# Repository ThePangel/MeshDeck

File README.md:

# MeshDeck

Standalone ESP32-S3 powered Meshtastic device!

---

Meshdeck is a Standalone Meshtastic device powered by an ESP32-S3, It has a built in keyboard and a touchscreen allowing you to communicate off grid without any phone, completely standalone.

I made this because I wanted to get into Meshtastic, and RF radio stuff, and the best way of learning is making

The keyboard is just a button matrix connected to an RP2040 which will act as an i2c slave and send keycodes to the esp. 

---

---

## Bill of Materials (BOM)

| Designator | Footprint                                | Quantity | Value           | LCSC Part #     |
|------------|------------------------------------------|----------|-----------------|-----------------|
| C1         | C0402                                    | 1        | 22uF            | C105226         |
| C10, C11, C12, C19 | C0402                            | 4        | 10uF            | C15525          |
| C13, C2, C20, C22, C23, C24, C25, C26, C27, C28, C30, C31, C32, C35, C36, C37, C38, C39, C4, C40, C41, C42, C43, C44, C45, C46, C47, C48, C49, C5, C50, C51, C52, C53, C54, C55, C56, C57, C58, C59, C60, C61, C62, C63, C64, C65, C66, C67, C68, C69, C70 | C0402 | 51 | 0.1uF | C1525 |
| C14, C15   | C0402                                    | 2        | 12pF            | C1547           |
| C16, C18, C21, C29, C3, C7 | C0402                   | 6        | 1uF             | C14445          |
| C17        | C0402                                    | 1        | 1Nf             | C1523           |
| C33, C34   | C0402                                    | 2        | 15pF            | C1548           |
| C6, C8, C9 | C0402                                    | 3        | 4.7 uF          | C23733          |
| CARD1      | TF-SMD_503398-1892                       | 1        | 503398-1892     | C428492         |
| CN1        | COMM-SMD_18P-L10.1-W9.7-P1.1-TL_L76-LB  | 1        | ATGM336H-6N-74  | C5804601        |
| D1         | SOT-666-6_L1.6-W1.2-P0.50-LS1.6-BR      | 1        | USBLC6-2P6      | C15999          |
| D10-D37    | SOD-123_L2.8-W1.8-LS3.7-RD              | 36       | 1N4148W T4      | C2099           |
| H1         | CONN-SMD_2P-P2.00_XUNPU_WAFER-PH2.0-2PWB| 1        | WAFER-PH2.0-2PWB| C3029440        |
| J1         | PinHeader_1x03_P2.54mm_Horizontal       | 1        | Conn_01x03_MountingPin | - |
| J2         | PinSocket_2x05_P2.54mm_Horizontal       | 1        | Conn_02x05_Odd_Even | - |
| L1         | L0402                                    | 1        | 0.47 µH         | C5788770        |
| L2         | L0402-RD                                 | 1        | 47nH            | C471397         |
| LED1, LED3 | LED0805-R-RD                             | 2        | 0805G (Green)   | C2297           |
| LED2       | LED0603-RD                               | 1        | Blue light 0603 | C2288           |
| LED4       | LED0402-RD                               | 1        | red             | C130719         |
| R1, R13, R17-R25 | R0402                              | 9        | 10KOhm          | C25531          |
| R10, R9    | R0402                                    | 2        | 1.8k            | C25871          |
| R11, R16   | R0402                                    | 2        | 10K             | C25744          |
| R12, R14, R15, R2-R4 | R0402                          | 6        | 0 Ohm           | C17168          |
| R19, R20   | R0402                                    | 2        | 220ohm          | C25091          |
| R26-R64    | R0402                                    | 37       | 1k              | C11702          |
| R5, R6     | R0402                                    | 2        | 5.1k            | C25905          |
| R62, R63   | R0603                                    | 2        | 100k            | C14675          |
| R7         | R0402                                    | 1        | 1.5K            | C25867          |
| R8         | R0402                                    | 1        | 1.5K            | C25867          |
| RF1, RF2   | SMA-SMD_HJ-SMA023                        | 2        | HJ-SMA023       | C1509219        |
| SW1-SW39   | SW-SMD_4P-L5.2-W5.2-P3.70-LS6.5         | 38       | 4*4*1.7         | C10852          |
| SW3        | KEY-TH_4P-L7.5-W6.8-P4.50-LS7.2         | 1        | SKHHLVA010      | C110289         |
| U1         | WIRELM-SMD_ESP32-S3-WROOM-1U            | 1        | ESP32-S3-WROOM-1U-N16R8 | C3013946 |
| U10        | CRYSTAL-SMD_4P-L3.2-W2.5-BL             | 1        | ABM8-272-T3_C20625731 | C20625731 |
| U2         | WIRELM-SMD_SX1278S165SY-T-X1            | 1        | SX1262S8S+T-X1  | C718838         |
| U3         | VSON-6_L1.5-W1.5-P0.50-TL               | 1        | TPS6282533DMQR  | C3189971        |
| U4         | QFN-16_L3.0-W3.0-P0.50-TL-EP1.7         | 1        | BQ24074RGTR     | C54313          |
| U5         | OSC-TH_BD2.0-P0.50                      | 1        | RN32768114      | C7206316        |
| U6         | 2.8 SPI LCD TFT ST7789                  | 1        | ~               | -               |
| U7         | SOIC-14_L8.7-W3.9-P1.27-LS6.0-BL        | 1        | CD4013BM        | C347580         |
| U8         | LQFN-56_L7.0-W7.0-P0.4-EP               | 1        | RP2040          | C2040           |
| U9         | SOIC-8_L5.3-W5.3-P1.27-LS8.0-BL         | 1        | W25Q128JVSIQTR  | C97521          |
| USBC1      | USB-C_SMD-TYPE-C-31-M-12_1              | 1        | TYPE-C-31-M-12  | C165948         |

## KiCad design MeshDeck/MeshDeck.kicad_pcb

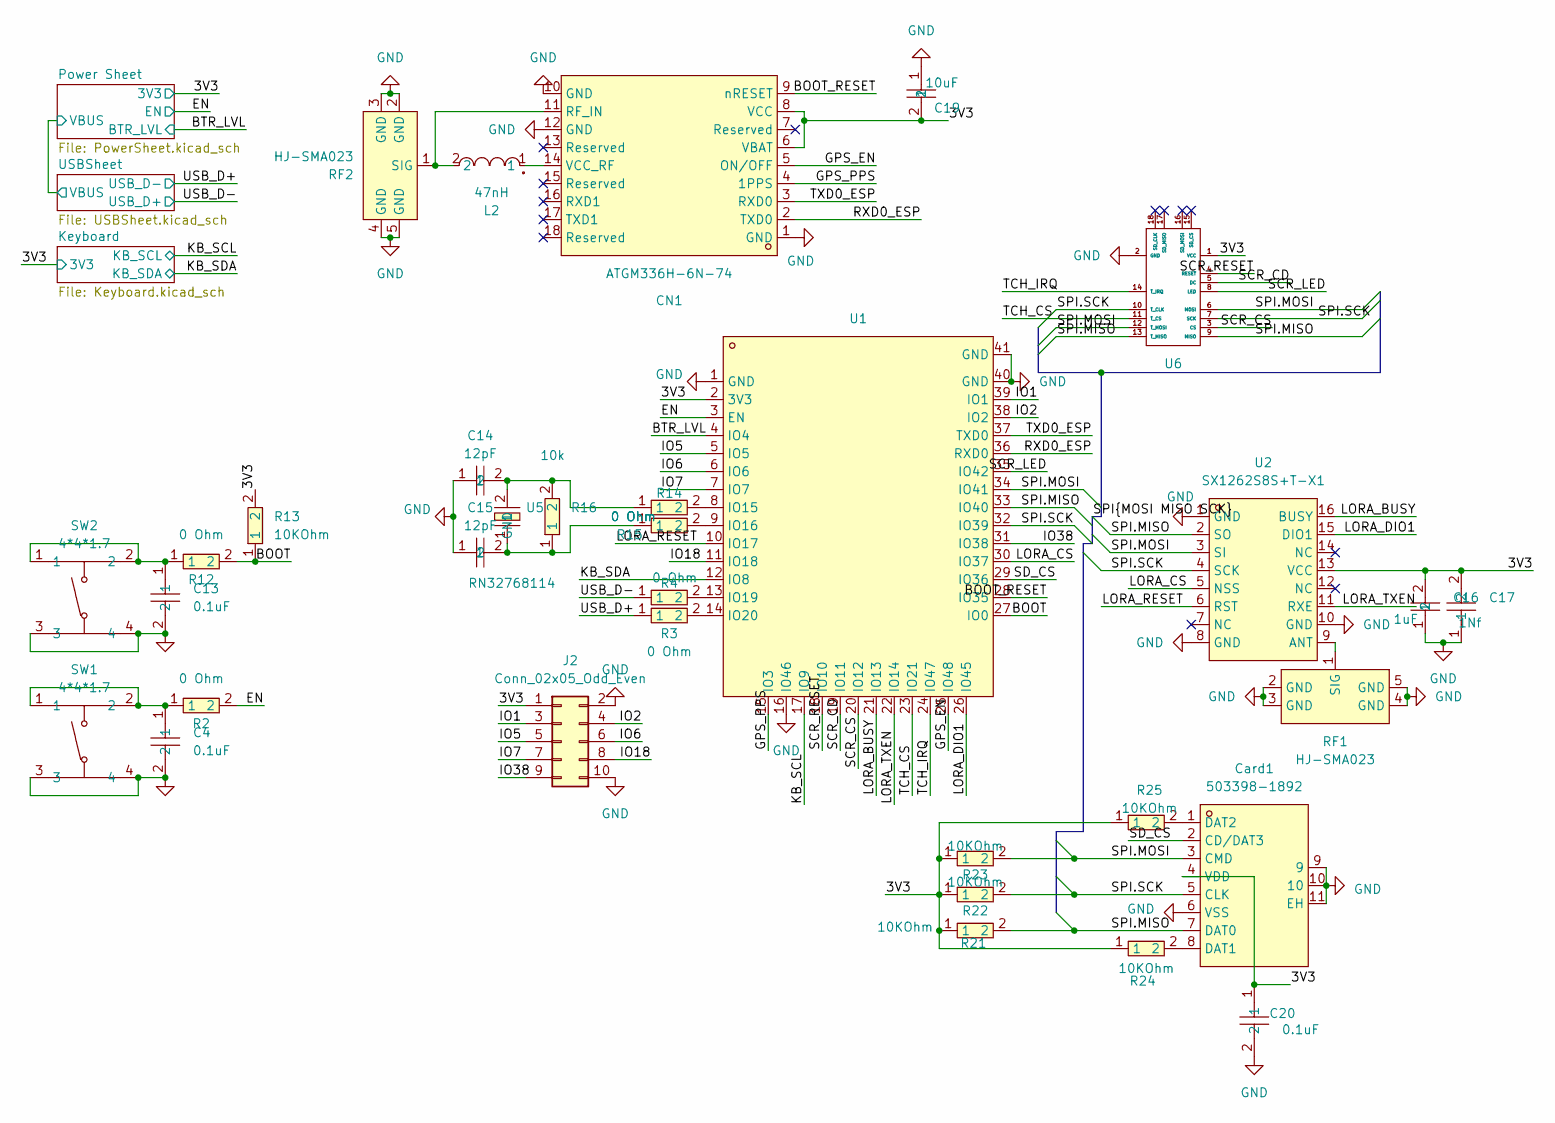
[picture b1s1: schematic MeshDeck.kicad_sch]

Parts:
C4, C13, C20: 0.1uF; C0402; LCSC Part C1525
C14, C15: 12pF; C0402; LCSC Part C1547
C16: 1uF; C0402; LCSC Part C14445
C17: 1Nf; C0402; LCSC Part C1523
C19: 10uF; C0402; LCSC Part C15525
CN1: ATGM336H-6N-74; COMM-SMD_18P-L10.1-W9.7-P1.1-TL_L76-LB; LCSC Part C5804601
Card1: 503398-1892; TF-SMD_503398-1892; LCSC Part C428492
J2: Conn_02x05_Odd_Even; PinSocket_2x05_P2.54mm_Horizontal
L2: 47nH; L0402-RD; LCSC Part C471397
R2, R3, R4, R12, R14, R15: 0 Ohm; R0402; LCSC Part C17168
R13, R21, R22, R23, R24, R25: 10KOhm; R0402; LCSC Part C25531
R16: 10k; R0402; LCSC Part C25744
RF1, RF2: HJ-SMA023; SMA-SMD_HJ-SMA023; LCSC Part C1509219
SW1, SW2: 4*4*1.7; SW-SMD_4P-L5.2-W5.2-P3.70-LS6.5; LCSC Part C10852
U1: ESP32-S3-WROOM-1U-N16R8; WIRELM-SMD_ESP32-S3-WROOM-1U; LCSC Part C3013946
U2: SX1262S8S+T-X1; WIRELM-SMD_SX1278S165SY-T-X1; LCSC Part C718838
U5: RN32768114; OSC-TH_BD2.0-P0.50; LCSC Part C7206316
U6: 2.8 SPI LCD TFT ST7789

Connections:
/3V3: C16.2, C17.2, C19.2, C20.1, CN1.6 (VBAT), CN1.8 (VCC), Card1.4 (VDD), J2.1, R13.2, R21.1, R22.1, R23.1, R24.1, R25.1, U1.2 (3V3), U2.13 (VCC), U6.1 (VCC); also elsewhere on the board
/BOOT: R12.2, R13.1, U1.27 (IO0)
/BOOT_RESET: CN1.9 (nRESET), U1.28 (IO35)
/BTR_LVL: U1.4 (IO4); also elsewhere on the board
/EN: R2.2, U1.3 (EN); also elsewhere on the board
/GPS_EN: CN1.5 (ON/OFF), U1.25 (IO48)
/GPS_PPS: CN1.4 (1PPS), U1.15 (IO3)
/IO1: J2.3, U1.39 (IO1)
/IO2: J2.4, U1.38 (IO2)
/IO5: J2.5, U1.5 (IO5)
/IO6: J2.6, U1.6 (IO6)
/IO7: J2.7, U1.7 (IO7)
/IO18: J2.8, U1.11 (IO18)
/IO38: J2.9, U1.31 (IO38)
/KB_SCL: U1.17 (IO9); also elsewhere on the board
/KB_SDA: U1.12 (IO8); also elsewhere on the board
/LORA_BUSY: U1.21 (IO13), U2.16 (BUSY)
/LORA_CS: U1.30 (IO37), U2.5 (NSS)
/LORA_DIO1: U1.26 (IO45), U2.15 (DIO1)
/LORA_RESET: U1.10 (IO17), U2.6 (RST)
/LORA_TXEN: U1.22 (IO14), U2.11 (RXE)
/RXD0_ESP: CN1.2 (TXD0), U1.36 (RXD0)
/SCR_CD: U1.19 (IO11), U6.5 (DC)
/SCR_CS: U1.20 (IO12), U6.3 (CS)
/SCR_LED: U1.35 (IO42), U6.8 (LED)
/SCR_RESET: U1.18 (IO10), U6.4 (RESET)
/SD_CS: Card1.2 (CD/DAT3), U1.29 (IO36)
/SPI.MISO: Card1.7 (DAT0), R21.2, U1.33 (IO40), U2.2 (SO), U6.9 (MISO), U6.13 (T_MISO)
/SPI.MOSI: Card1.3 (CMD), R23.2, U1.34 (IO41), U2.3 (SI), U6.6 (MOSI), U6.12 (T_MOSI)
/SPI.SCK: Card1.5 (CLK), R22.2, U1.32 (IO39), U2.4 (SCK), U6.7 (SCK), U6.10 (T_CLK)
/TCH_CS: U1.23 (IO21), U6.11 (T_CS)
/TCH_IRQ: U1.24 (IO47), U6.14 (T_IRQ)
/TXD0_ESP: CN1.3 (RXD0), U1.37 (TXD0)
/USB_D+: R3.1; also elsewhere on the board
/USB_D-: R4.1; also elsewhere on the board
GND: C4.2, C13.2, C14.1, C15.1, C16.1, C17.1, C19.1, C20.2, CN1.1 (GND), CN1.10 (GND), CN1.12 (GND), Card1.6 (VSS), Card1.9, Card1.10, Card1.11 (EH), J2.2, J2.10, RF1.2 (GND), RF1.3 (GND), RF1.4 (GND), RF1.5 (GND), RF2.2 (GND), RF2.3 (GND), RF2.4 (GND), RF2.5 (GND), SW1.3, SW1.4, SW2.3, SW2.4, U1.1 (GND), U1.16 (IO46), U1.40 (GND), U1.41 (GND), U2.1 (GND), U2.8 (GND), U2.10 (GND), U6.2 (GND); also elsewhere on the board
unnamed: C4.1, R2.1, SW1.1, SW1.2
unnamed: C13.1, R12.1, SW2.1, SW2.2
unnamed: C15.2, R15.1, R16.1, U5.1
unnamed: CN1.11 (RF_IN), L2.2, RF2.1 (SIG)
unnamed: CN1.14 (VCC_RF), L2.1
unnamed: Card1.8 (DAT1), R24.2
unnamed: Card1.1 (DAT2), R25.2
unnamed: RF1.1 (SIG), U2.9 (ANT)
unnamed: R14.2, U1.8 (IO15)
unnamed: R15.2, U1.9 (IO16)
unnamed: R4.2, U1.13 (IO19)
unnamed: R3.2, U1.14 (IO20)
unnamed: C14.2, R14.1, R16.2, U5.2 (GND)

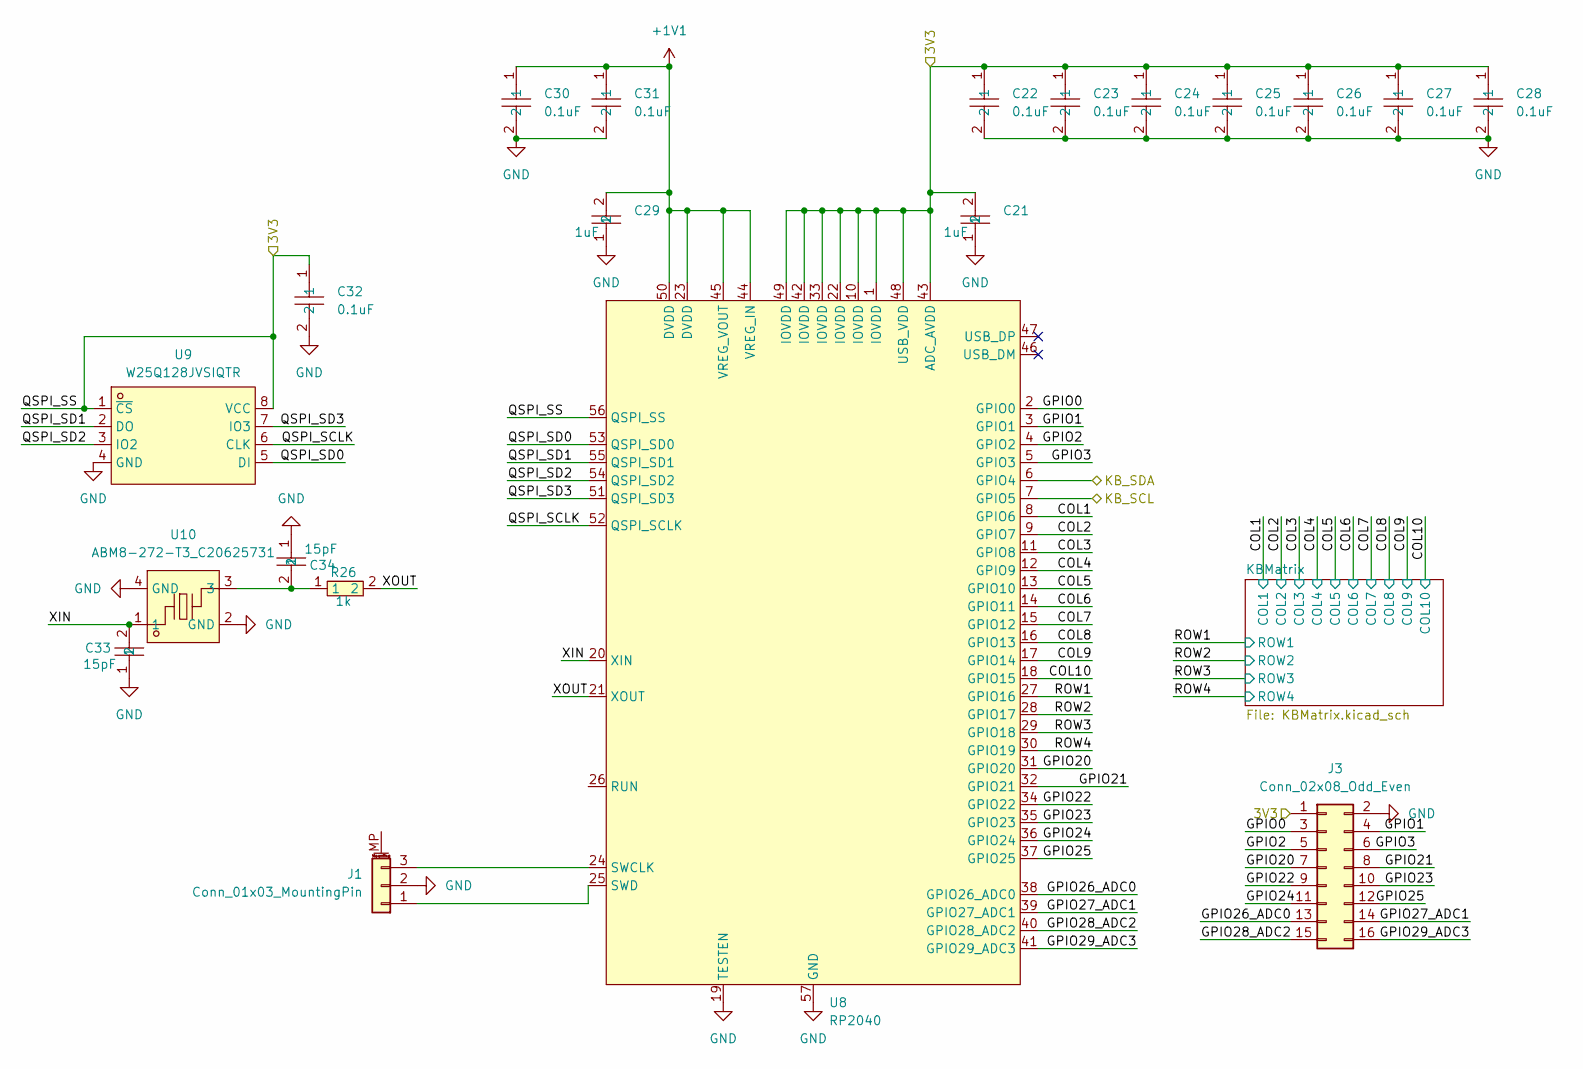
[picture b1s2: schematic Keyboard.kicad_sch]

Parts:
C21, C29: 1uF; C0402; LCSC Part C14445
C22, C23, C24, C25, C26, C27, C28, C30, C31, C32: 0.1uF; C0402; LCSC Part C1525
C33, C34: 15pF; C0402; LCSC Part C1548
J1: Conn_01x03_MountingPin; PinHeader_1x03_P2.54mm_Horizontal
J3: Conn_02x08_Odd_Even; PinSocket_2x08_P2.54mm_Horizontal
R26: 1k; R0402; LCSC Part C11702
U8: RP2040; LQFN-56_L7.0-W7.0-P0.4-EP; LCSC Part C2040
U9: W25Q128JVSIQTR; SOIC-8_L5.3-W5.3-P1.27-LS8.0-BL; LCSC Part C97521
U10: ABM8-272-T3_C20625731; CRYSTAL-SMD_4P-L3.2-W2.5-BL; LCSC Part C20625731

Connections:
+1V1: C29.2, C30.1, C31.1, U8.23 (DVDD), U8.44 (VREG_IN), U8.45 (VREG_VOUT), U8.50 (DVDD)
/3V3: C21.2, C22.1, C23.1, C24.1, C25.1, C26.1, C27.1, C28.1, C32.1, J3.1, U8.1 (IOVDD), U8.10 (IOVDD), U8.22 (IOVDD), U8.33 (IOVDD), U8.42 (IOVDD), U8.43 (ADC_AVDD), U8.48 (USB_VDD), U8.49 (IOVDD), U8.56 (QSPI_SS), U9.1 (~CS), U9.8 (VCC); also elsewhere on the board
/KB_SCL: U8.7 (GPIO5); also elsewhere on the board
/KB_SDA: U8.6 (GPIO4); also elsewhere on the board
/Keyboard/COL1: U8.8 (GPIO6); also elsewhere on the board
/Keyboard/COL2: U8.9 (GPIO7); also elsewhere on the board
/Keyboard/COL3: U8.11 (GPIO8); also elsewhere on the board
/Keyboard/COL4: U8.12 (GPIO9); also elsewhere on the board
/Keyboard/COL5: U8.13 (GPIO10); also elsewhere on the board
/Keyboard/COL6: U8.14 (GPIO11); also elsewhere on the board
/Keyboard/COL7: U8.15 (GPIO12); also elsewhere on the board
/Keyboard/COL8: U8.16 (GPIO13); also elsewhere on the board
/Keyboard/COL9: U8.17 (GPIO14); also elsewhere on the board
/Keyboard/COL10: U8.18 (GPIO15); also elsewhere on the board
/Keyboard/GPIO0: J3.3, U8.2 (GPIO0)
/Keyboard/GPIO1: J3.4, U8.3 (GPIO1)
/Keyboard/GPIO2: J3.5, U8.4 (GPIO2)
/Keyboard/GPIO3: J3.6, U8.5 (GPIO3)
/Keyboard/GPIO20: J3.7, U8.31 (GPIO20)
/Keyboard/GPIO21: J3.8, U8.32 (GPIO21)
/Keyboard/GPIO22: J3.9, U8.34 (GPIO22)
/Keyboard/GPIO23: J3.10, U8.35 (GPIO23)
/Keyboard/GPIO24: J3.11, U8.36 (GPIO24)
/Keyboard/GPIO25: J3.12, U8.37 (GPIO25)
/Keyboard/GPIO26_ADC0: J3.13, U8.38 (GPIO26_ADC0)
/Keyboard/GPIO27_ADC1: J3.14, U8.39 (GPIO27_ADC1)
/Keyboard/GPIO28_ADC2: J3.15, U8.40 (GPIO28_ADC2)
/Keyboard/GPIO29_ADC3: J3.16, U8.41 (GPIO29_ADC3)
/Keyboard/QSPI_SCLK: U8.52 (QSPI_SCLK), U9.6 (CLK)
/Keyboard/QSPI_SD0: U8.53 (QSPI_SD0), U9.5 (DI)
/Keyboard/QSPI_SD1: U8.55 (QSPI_SD1), U9.2 (DO)
/Keyboard/QSPI_SD2: U8.54 (QSPI_SD2), U9.3 (IO2)
/Keyboard/QSPI_SD3: U8.51 (QSPI_SD3), U9.7 (IO3)
/Keyboard/ROW1: U8.27 (GPIO16); also elsewhere on the board
/Keyboard/ROW2: U8.28 (GPIO17); also elsewhere on the board
/Keyboard/ROW3: U8.29 (GPIO18); also elsewhere on the board
/Keyboard/ROW4: U8.30 (GPIO19); also elsewhere on the board
/Keyboard/XIN: C33.2, U8.20 (XIN), U10.1
/Keyboard/XOUT: R26.2, U8.21 (XOUT)
GND: C21.1, C22.2, C23.2, C24.2, C25.2, C26.2, C27.2, C28.2, C29.1, C30.2, C31.2, C32.2, C33.1, C34.1, J1.2, J3.2, U8.19 (TESTEN), U8.57 (GND), U9.4 (GND), U10.2 (GND), U10.4 (GND); also elsewhere on the board
unnamed: C34.2, R26.1, U10.3
unnamed: J1.1, U8.25 (SWD)
unnamed: J1.3, U8.24 (SWCLK)

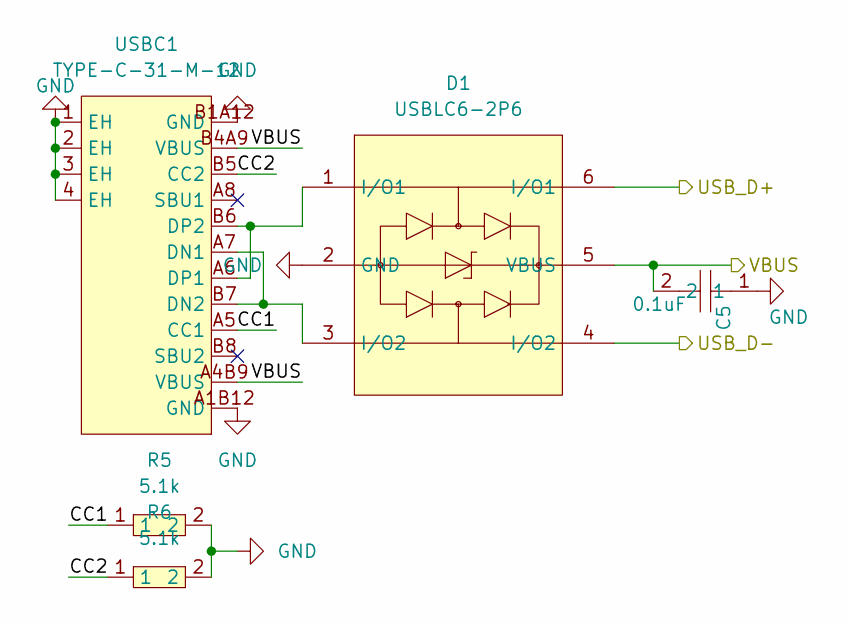
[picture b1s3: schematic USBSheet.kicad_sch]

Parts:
C5: 0.1uF; C0402; LCSC Part C1525
D1: USBLC6-2P6; SOT-666-6_L1.6-W1.2-P0.50-LS1.6-BR; LCSC Part C15999
R5, R6: 5.1k; R0402; LCSC Part C25905
USBC1: TYPE-C-31-M-12; USB-C_SMD-TYPE-C-31-M-12_1; LCSC Part C165948

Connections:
/USBSheet/CC1: R5.1, USBC1.A5 (CC1)
/USBSheet/CC2: R6.1, USBC1.B5 (CC2)
/USBSheet/VBUS: C5.2, D1.5 (VBUS), USBC1.A4B9 (VBUS), USBC1.B4A9 (VBUS); also elsewhere on the board
/USB_D+: D1.4 (I/O2); also elsewhere on the board
/USB_D-: D1.6 (I/O1); also elsewhere on the board
GND: C5.1, D1.2 (GND), R5.2, R6.2, USBC1.1 (EH), USBC1.2 (EH), USBC1.3 (EH), USBC1.4 (EH), USBC1.A1B12 (GND), USBC1.B1A12 (GND); also elsewhere on the board
unnamed: D1.3 (I/O2), USBC1.A7 (DN1), USBC1.B7 (DN2)
unnamed: D1.1 (I/O1), USBC1.A6 (DP1), USBC1.B6 (DP2)

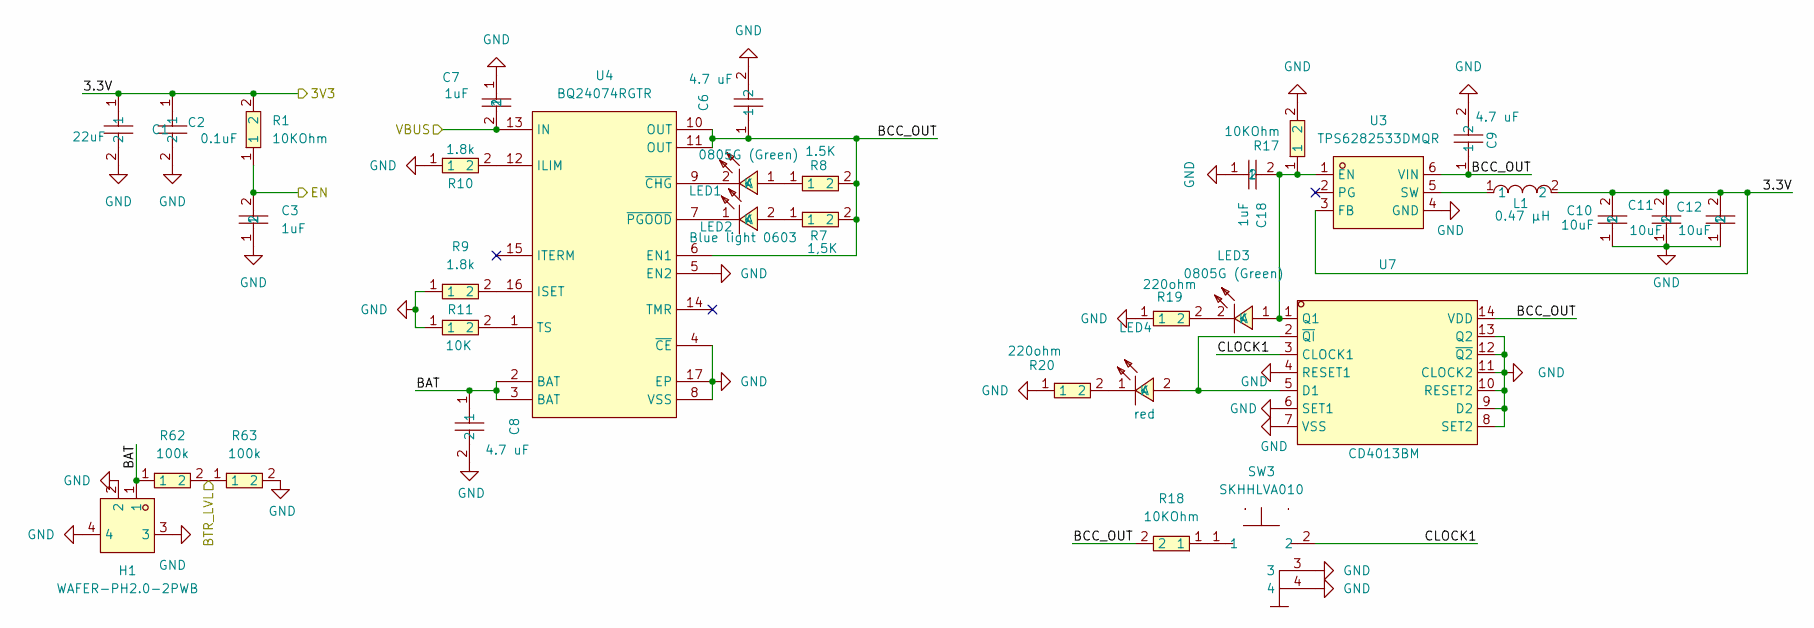
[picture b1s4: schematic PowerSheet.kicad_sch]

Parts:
C1: 22uF; C0402; LCSC Part C105226
C2: 0.1uF; C0402; LCSC Part C1525
C3, C7, C18: 1uF; C0402; LCSC Part C14445
C6, C8, C9: 4.7 uF; C0402; LCSC Part C23733
C10, C11, C12: 10uF; C0402; LCSC Part C15525
H1: WAFER-PH2.0-2PWB; CONN-SMD_2P-P2.00_XUNPU_WAFER-PH2.0-2PWB; LCSC Part C3029440
L1: 0.47 µH; L0402; LCSC Part C5788770
LED1, LED3: 0805G (Green); LED0805-R-RD; LCSC Part C2297
LED2: Blue light 0603; LED0603-RD; LCSC Part C2288
LED4: red; LED0402-RD; LCSC Part C130719
R1, R17, R18: 10KOhm; R0402; LCSC Part C25531
R7: 1,5K; R0402; LCSC Part C25867
R8: 1.5K; R0402; LCSC Part C25867
R9, R10: 1.8k; R0402; LCSC Part C25871
R11: 10K; R0402; LCSC Part C25744
R19, R20: 220ohm; R0402; LCSC Part C25091
R62, R63: 100k; R0603; LCSC Part C14675
SW3: SKHHLVA010; KEY-TH_4P-L7.5-W6.8-P4.50-LS7.2; LCSC Part C110289
U3: TPS6282533DMQR; VSON-6_L1.5-W1.5-P0.50-TL; LCSC Part C3189971
U4: BQ24074RGTR; QFN-16_L3.0-W3.0-P0.50-TL-EP1.7; LCSC Part C54313
U7: CD4013BM; SOIC-14_L8.7-W3.9-P1.27-LS6.0-BL; LCSC Part C347580

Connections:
/3V3: C1.1, C2.1, C10.2, C11.2, C12.2, L1.2, R1.2, U3.3 (FB); also elsewhere on the board
/BTR_LVL: R62.2, R63.1; also elsewhere on the board
/EN: C3.2, R1.1; also elsewhere on the board
/Power Sheet/BAT: C8.1, H1.1, R62.1, U4.2 (BAT), U4.3 (BAT)
/Power Sheet/BCC_OUT: C6.1, C9.1, R7.2, R8.2, R18.2, U3.6 (VIN), U4.6 (EN1), U4.10 (OUT), U4.11 (OUT), U7.14 (VDD)
/Power Sheet/CLOCK1: SW3.2, U7.3 (CLOCK1)
/USBSheet/VBUS: C7.2, U4.13 (IN); also elsewhere on the board
GND: C1.2, C2.2, C3.1, C6.2, C7.1, C8.2, C9.2, C10.1, C11.1, C12.1, C18.1, H1.2, H1.3, H1.4, R9.1, R10.1, R11.1, R17.2, R19.1, R20.1, R63.2, SW3.3, SW3.4, U3.4 (GND), U4.4 (~CE), U4.5 (EN2), U4.8 (VSS), U4.17 (EP), U7.4 (RESET1), U7.6 (SET1), U7.7 (VSS), U7.8 (SET2), U7.9 (D2), U7.10 (RESET2), U7.11 (CLOCK2), U7.12 (~Q2), U7.13 (Q2); also elsewhere on the board
unnamed: LED1.1 (A), R8.1
unnamed: LED1.2 (K), U4.9 (~CHG)
unnamed: LED2.2 (A), R7.1
unnamed: LED2.1 (K), U4.7 (~PGOOD)
unnamed: C18.2, LED3.1 (A), R17.1, U3.1 (EN), U7.1 (Q1)
unnamed: LED3.2 (K), R19.2
unnamed: LED4.2 (A), U7.2 (~QI), U7.5 (D1)
unnamed: LED4.1 (K), R20.2
unnamed: R18.1, SW3.1
unnamed: L1.1, U3.5 (SW)
unnamed: R10.2, U4.12 (ILIM)
unnamed: R9.2, U4.16 (ISET)
unnamed: R11.2, U4.1 (TS)

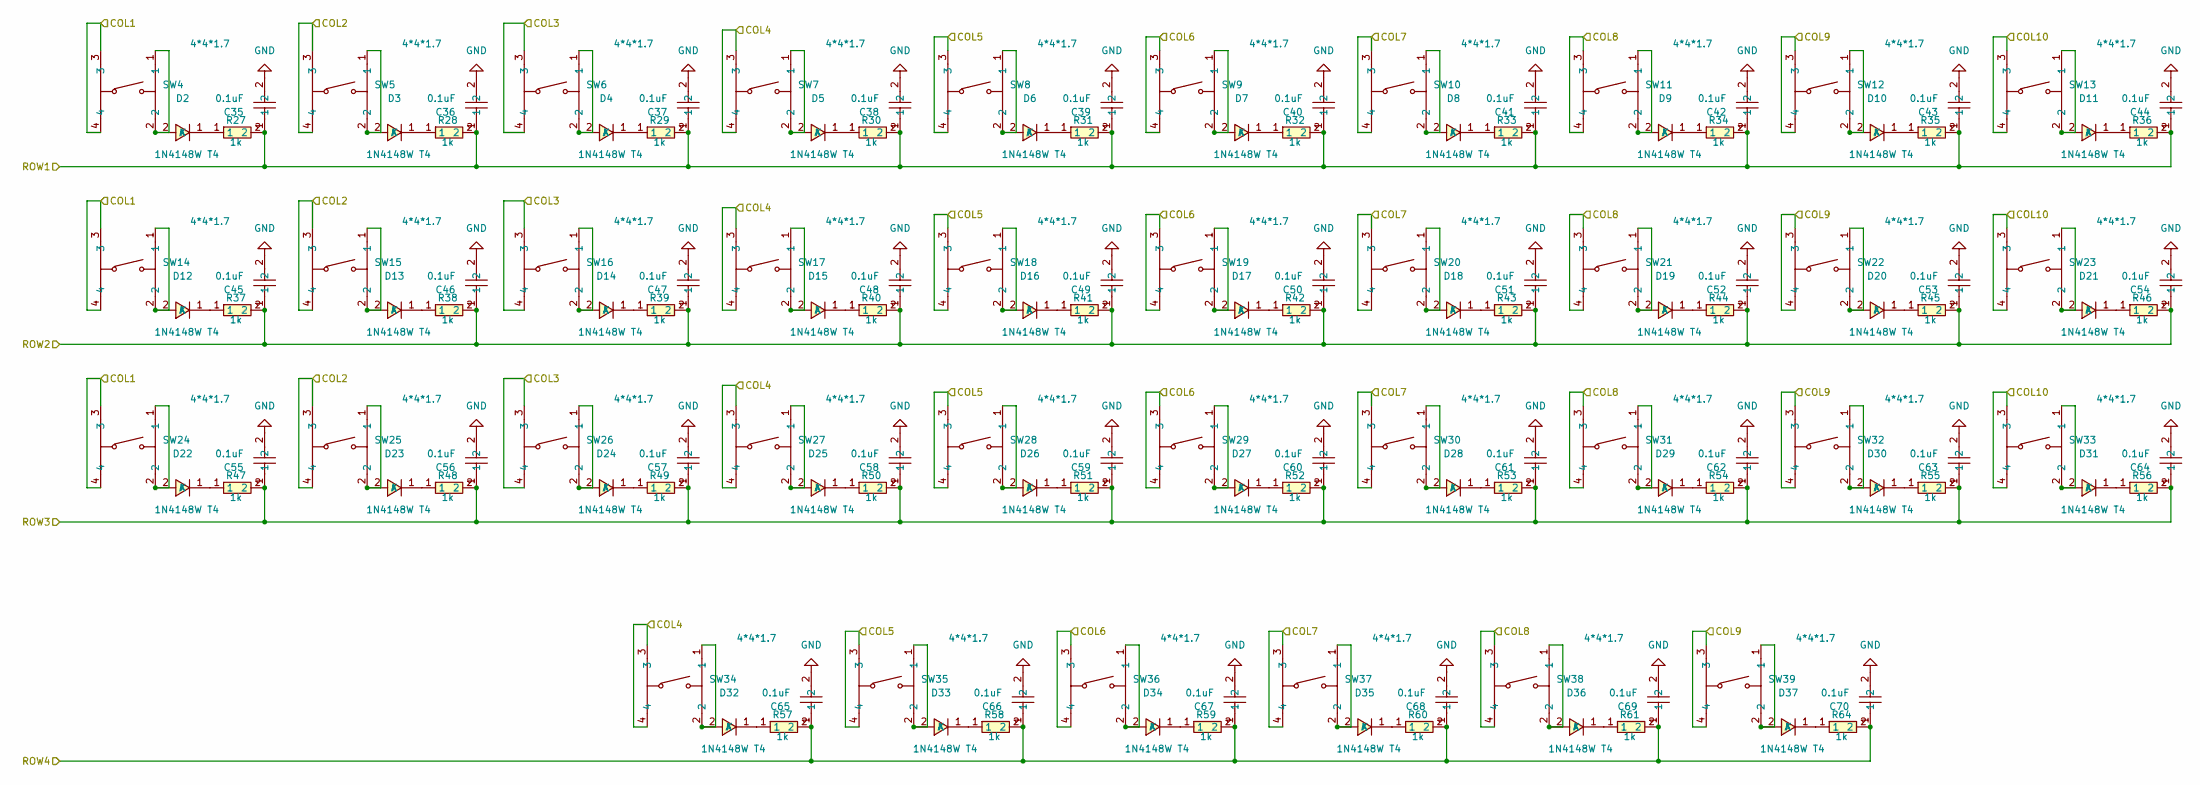
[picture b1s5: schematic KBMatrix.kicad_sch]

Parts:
C35, C36, C37, C38, C39, C40, C41, C42, C43, C44, C45, C46, C47, C48, C49, C50, C51, C52, C53, C54, C55, C56, C57, C58, C59, C60, C61, C62, C63, C64, C65, C66, C67, C68, C69, C70: 0.1uF; C0402; LCSC Part C1525
D2, D3, D4, D5, D6, D7, D8, D9, D10, D11, D12, D13, D14, D15, D16, D17, D18, D19, D20, D21, D22, D23, D24, D25, D26, D27, D28, D29, D30, D31, D32, D33, D34, D35, D36, D37: 1N4148W T4; SOD-123_L2.8-W1.8-LS3.7-RD; LCSC Part C2099
R27, R28, R29, R30, R31, R32, R33, R34, R35, R36, R37, R38, R39, R40, R41, R42, R43, R44, R45, R46, R47, R48, R49, R50, R51, R52, R53, R54, R55, R56, R57, R58, R59, R60, R61, R64: 1k; R0402; LCSC Part C11702
SW4, SW5, SW6, SW7, SW8, SW9, SW10, SW11, SW12, SW13, SW14, SW15, SW16, SW17, SW18, SW19, SW20, SW21, SW22, SW23, SW24, SW25, SW26, SW27, SW28, SW29, SW30, SW31, SW32, SW33, SW34, SW35, SW36, SW37, SW38, SW39: 4*4*1.7; SW-SMD_4P-L5.2-W5.2-P3.70-LS6.5; LCSC Part C10852

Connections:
/Keyboard/COL1: SW4.3, SW4.4, SW14.3, SW14.4, SW24.3, SW24.4; also elsewhere on the board
/Keyboard/COL2: SW5.3, SW5.4, SW15.3, SW15.4, SW25.3, SW25.4; also elsewhere on the board
/Keyboard/COL3: SW6.3, SW6.4, SW16.3, SW16.4, SW26.3, SW26.4; also elsewhere on the board
/Keyboard/COL4: SW7.3, SW7.4, SW17.3, SW17.4, SW27.3, SW27.4, SW34.3, SW34.4; also elsewhere on the board
/Keyboard/COL5: SW8.3, SW8.4, SW18.3, SW18.4, SW28.3, SW28.4, SW35.3, SW35.4; also elsewhere on the board
/Keyboard/COL6: SW9.3, SW9.4, SW19.3, SW19.4, SW29.3, SW29.4, SW36.3, SW36.4; also elsewhere on the board
/Keyboard/COL7: SW10.3, SW10.4, SW20.3, SW20.4, SW30.3, SW30.4, SW37.3, SW37.4; also elsewhere on the board
/Keyboard/COL8: SW11.3, SW11.4, SW21.3, SW21.4, SW31.3, SW31.4, SW38.3, SW38.4; also elsewhere on the board
/Keyboard/COL9: SW12.3, SW12.4, SW22.3, SW22.4, SW32.3, SW32.4, SW39.3, SW39.4; also elsewhere on the board
/Keyboard/COL10: SW13.3, SW13.4, SW23.3, SW23.4, SW33.3, SW33.4; also elsewhere on the board
/Keyboard/ROW1: C35.1, C36.1, C37.1, C38.1, C39.1, C40.1, C41.1, C42.1, C43.1, C44.1, R27.2, R28.2, R29.2, R30.2, R31.2, R32.2, R33.2, R34.2, R35.2, R36.2; also elsewhere on the board
/Keyboard/ROW2: C45.1, C46.1, C47.1, C48.1, C49.1, C50.1, C51.1, C52.1, C53.1, C54.1, R37.2, R38.2, R39.2, R40.2, R41.2, R42.2, R43.2, R44.2, R45.2, R46.2; also elsewhere on the board
/Keyboard/ROW3: C55.1, C56.1, C57.1, C58.1, C59.1, C60.1, C61.1, C62.1, C63.1, C64.1, R47.2, R48.2, R49.2, R50.2, R51.2, R52.2, R53.2, R54.2, R55.2, R56.2; also elsewhere on the board
/Keyboard/ROW4: C65.1, C66.1, C67.1, C68.1, C69.1, C70.1, R57.2, R58.2, R59.2, R60.2, R61.2, R64.2; also elsewhere on the board
GND: C35.2, C36.2, C37.2, C38.2, C39.2, C40.2, C41.2, C42.2, C43.2, C44.2, C45.2, C46.2, C47.2, C48.2, C49.2, C50.2, C51.2, C52.2, C53.2, C54.2, C55.2, C56.2, C57.2, C58.2, C59.2, C60.2, C61.2, C62.2, C63.2, C64.2, C65.2, C66.2, C67.2, C68.2, C69.2, C70.2; also elsewhere on the board
unnamed: D2.2 (A), SW4.1, SW4.2
unnamed: D2.1 (K), R27.1
unnamed: D3.2 (A), SW5.1, SW5.2
unnamed: D3.1 (K), R28.1
unnamed: D4.2 (A), SW6.1, SW6.2
unnamed: D4.1 (K), R29.1
unnamed: D5.2 (A), SW7.1, SW7.2
unnamed: D5.1 (K), R30.1
unnamed: D6.2 (A), SW8.1, SW8.2
unnamed: D6.1 (K), R31.1
unnamed: D7.2 (A), SW9.1, SW9.2
unnamed: D7.1 (K), R32.1
unnamed: D8.2 (A), SW10.1, SW10.2
unnamed: D8.1 (K), R33.1
unnamed: D9.2 (A), SW11.1, SW11.2
unnamed: D9.1 (K), R34.1
unnamed: D10.2 (A), SW12.1, SW12.2
unnamed: D10.1 (K), R35.1
unnamed: D11.2 (A), SW13.1, SW13.2
unnamed: D11.1 (K), R36.1
unnamed: D12.2 (A), SW14.1, SW14.2
unnamed: D12.1 (K), R37.1
unnamed: D13.2 (A), SW15.1, SW15.2
unnamed: D13.1 (K), R38.1
unnamed: D14.2 (A), SW16.1, SW16.2
unnamed: D14.1 (K), R39.1
unnamed: D15.2 (A), SW17.1, SW17.2
unnamed: D15.1 (K), R40.1
unnamed: D16.2 (A), SW18.1, SW18.2
unnamed: D16.1 (K), R41.1
unnamed: D17.2 (A), SW19.1, SW19.2
unnamed: D17.1 (K), R42.1
unnamed: D18.2 (A), SW20.1, SW20.2
unnamed: D18.1 (K), R43.1
unnamed: D19.2 (A), SW21.1, SW21.2
unnamed: D19.1 (K), R44.1
unnamed: D20.2 (A), SW22.1, SW22.2
unnamed: D20.1 (K), R45.1
unnamed: D21.2 (A), SW23.1, SW23.2
unnamed: D21.1 (K), R46.1
unnamed: D22.2 (A), SW24.1, SW24.2
unnamed: D22.1 (K), R47.1
unnamed: D23.2 (A), SW25.1, SW25.2
unnamed: D23.1 (K), R48.1
unnamed: D24.2 (A), SW26.1, SW26.2
unnamed: D24.1 (K), R49.1
unnamed: D25.2 (A), SW27.1, SW27.2
unnamed: D25.1 (K), R50.1
unnamed: D26.2 (A), SW28.1, SW28.2
unnamed: D26.1 (K), R51.1
unnamed: D27.2 (A), SW29.1, SW29.2
unnamed: D27.1 (K), R52.1
unnamed: D28.2 (A), SW30.1, SW30.2
unnamed: D28.1 (K), R53.1
unnamed: D29.2 (A), SW31.1, SW31.2
unnamed: D29.1 (K), R54.1
unnamed: D30.2 (A), SW32.1, SW32.2
unnamed: D30.1 (K), R55.1
unnamed: D31.2 (A), SW33.1, SW33.2
unnamed: D31.1 (K), R56.1
unnamed: D32.2 (A), SW34.1, SW34.2
unnamed: D32.1 (K), R57.1
unnamed: D33.2 (A), SW35.1, SW35.2
unnamed: D33.1 (K), R58.1
unnamed: D34.2 (A), SW36.1, SW36.2
unnamed: D34.1 (K), R59.1
unnamed: D35.2 (A), SW37.1, SW37.2
unnamed: D35.1 (K), R60.1
unnamed: D36.2 (A), SW38.1, SW38.2
unnamed: D36.1 (K), R61.1
unnamed: D37.2 (A), SW39.1, SW39.2
unnamed: D37.1 (K), R64.1

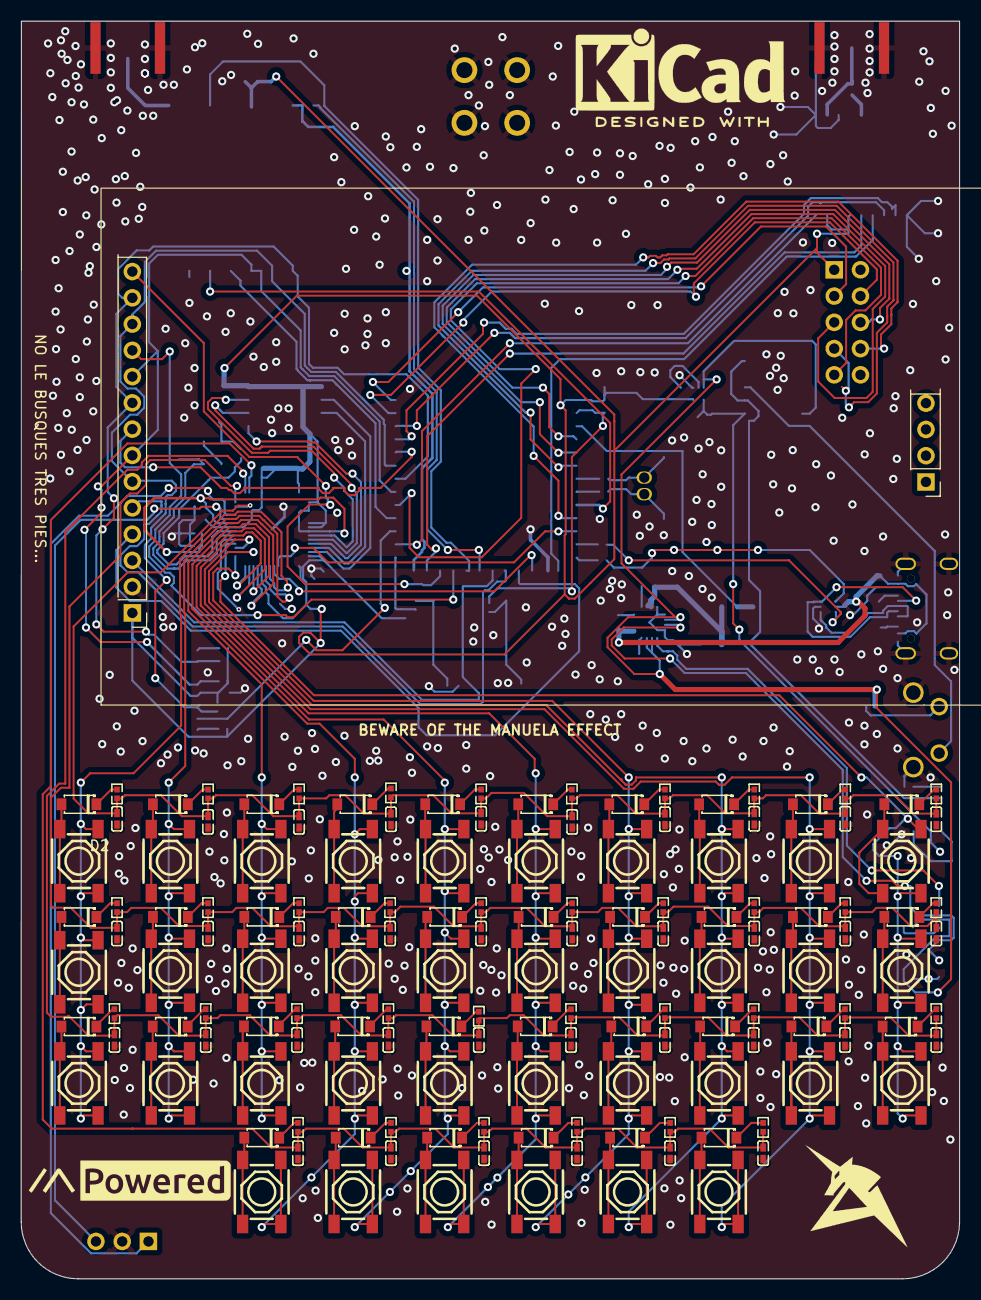
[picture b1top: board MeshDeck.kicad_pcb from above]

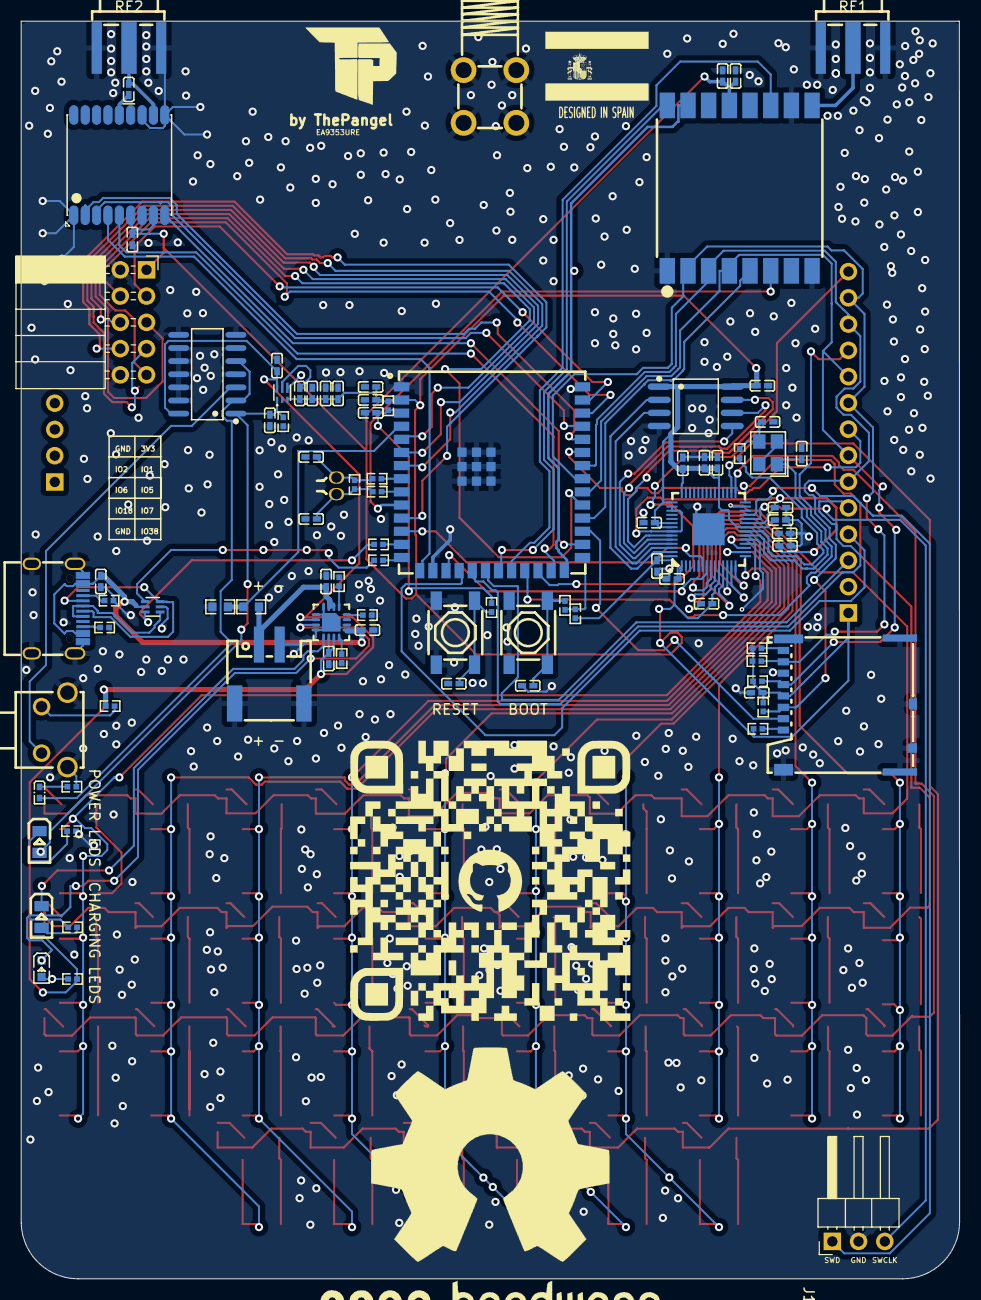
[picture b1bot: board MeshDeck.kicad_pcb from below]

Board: 4 copper layers, 90.8 x 121.7 mm, 234 parts (89 on the bottom side), 167 nets.

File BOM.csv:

Designator,Footprint,Quantity,Value,LCSC Part #
C1,C0402,1,22uF,C105226
"C10, C11, C12, C19",C0402,4,10uF,C15525
"C13, C2, C20, C22, C23, C24, C25, C26, C27, C28, C30, C31, C32, C35, C36, C37, C38, C39, C4, C40, C41, C42, C43, C44, C45, C46, C47, C48, C49, C5, C50, C51, C52, C53, C54, C55, C56, C57, C58, C59, C60, C61, C62, C63, C64, C65, C66, C67, C68, C69, C70",C0402,51,0.1uF,C1525
"C14, C15",C0402,2,12pF,C1547
"C16, C18, C21, C29, C3, C7",C0402,6,1uF,C14445
C17,C0402,1,1Nf,C1523
"C33, C34",C0402,2,15pF,C1548
"C6, C8, C9",C0402,3,4.7 uF,C23733
CARD1,TF-SMD_503398-1892,1,503398-1892,C428492
CN1,COMM-SMD_18P-L10.1-W9.7-P1.1-TL_L76-LB,1,ATGM336H-6N-74,C5804601
D1,SOT-666-6_L1.6-W1.2-P0.50-LS1.6-BR,1,USBLC6-2P6,C15999
"D10, D11, D12, D13, D14, D15, D16, D17, D18, D19, D2, D20, D21, D22, D23, D24, D25, D26, D27, D28, D29, D3, D30, D31, D32, D33, D34, D35, D36, D37, D4, D5, D6, D7, D8, D9",SOD-123_L2.8-W1.8-LS3.7-RD,36,1N4148W T4,C2099
H1,CONN-SMD_2P-P2.00_XUNPU_WAFER-PH2.0-2PWB,1,WAFER-PH2.0-2PWB,C3029440
J1,PinHeader_1x03_P2.54mm_Horizontal,1,Conn_01x03_MountingPin,
J2,PinSocket_2x05_P2.54mm_Horizontal,1,Conn_02x05_Odd_Even,
L1,L0402,1,0.47 µH,C5788770
L2,L0402-RD,1,47nH,C471397
"LED1, LED3",LED0805-R-RD,2,0805G (Green),C2297
LED2,LED0603-RD,1,Blue light 0603,C2288
LED4,LED0402-RD,1,red,C130719
"R1, R13, R17, R18, R21, R22, R23, R24, R25",R0402,9,10KOhm,C25531
"R10, R9",R0402,2,1.8k,C25871
"R11, R16",R0402,2,10K,C25744
"R12, R14, R15, R2, R3, R4",R0402,6,0 Ohm,C17168
"R19, R20",R0402,2,220ohm,C25091
"R26, R27, R28, R29, R30, R31, R32, R33, R34, R35, R36, R37, R38, R39, R40, R41, R42, R43, R44, R45, R46, R47, R48, R49, R50, R51, R52, R53, R54, R55, R56, R57, R58, R59, R60, R61, R64",R0402,37,1k,C11702
"R5, R6",R0402,2,5.1k,C25905
"R62, R63",R0603,2,100k,C14675
R7,R0402,1,"1,5K",C25867
R8,R0402,1,1.5K,C25867
"RF1, RF2",SMA-SMD_HJ-SMA023,2,HJ-SMA023,C1509219
"SW1, SW10, SW11, SW12, SW13, SW14, SW15, SW16, SW17, SW18, SW19, SW2, SW20, SW21, SW22, SW23, SW24, SW25, SW26, SW27, SW28, SW29, SW30, SW31, SW32, SW33, SW34, SW35, SW36, SW37, SW38, SW39, SW4, SW5, SW6, SW7, SW8, SW9",SW-SMD_4P-L5.2-W5.2-P3.70-LS6.5,38,4*4*1.7,C10852
SW3,KEY-TH_4P-L7.5-W6.8-P4.50-LS7.2,1,SKHHLVA010,C110289
U1,WIRELM-SMD_ESP32-S3-WROOM-1U,1,ESP32-S3-WROOM-1U-N16R8,C3013946
U10,CRYSTAL-SMD_4P-L3.2-W2.5-BL,1,ABM8-272-T3_C20625731,C20625731
U2,WIRELM-SMD_SX1278S165SY-T-X1,1,SX1262S8S+T-X1,C718838
U3,VSON-6_L1.5-W1.5-P0.50-TL,1,TPS6282533DMQR,C3189971
U4,QFN-16_L3.0-W3.0-P0.50-TL-EP1.7,1,BQ24074RGTR,C54313
U5,OSC-TH_BD2.0-P0.50,1,RN32768114,C7206316
U6,2.8 SPI LCD TFT ST7789,1,~,
U7,SOIC-14_L8.7-W3.9-P1.27-LS6.0-BL,1,CD4013BM,C347580
U8,LQFN-56_L7.0-W7.0-P0.4-EP,1,RP2040,C2040
U9,SOIC-8_L5.3-W5.3-P1.27-LS8.0-BL,1,W25Q128JVSIQTR,C97521
USBC1,USB-C_SMD-TYPE-C-31-M-12_1,1,TYPE-C-31-M-12,C165948

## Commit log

2025-11-03 Some initial components
2025-11-05 Added ESP-32 and USB stuff
2025-11-09 added charging ic circuit
2025-11-09 Added 3.3V step down converter
2025-11-09 Added oscillator, tidied up with subsheets and added boot btn
2025-11-10 set up LoRa module and screen (wip)
2025-11-10 Finished screen
2025-11-11 Added GPS and sof power button
2025-11-12 added sd card and started keyboard
2025-11-13 started pcb plus pin socket for expansion
2025-11-14 Wired kb matrix
2025-11-14 More routing
2025-11-14 Too much routing
2025-11-15 Finished PCB
2025-11-15 readme
